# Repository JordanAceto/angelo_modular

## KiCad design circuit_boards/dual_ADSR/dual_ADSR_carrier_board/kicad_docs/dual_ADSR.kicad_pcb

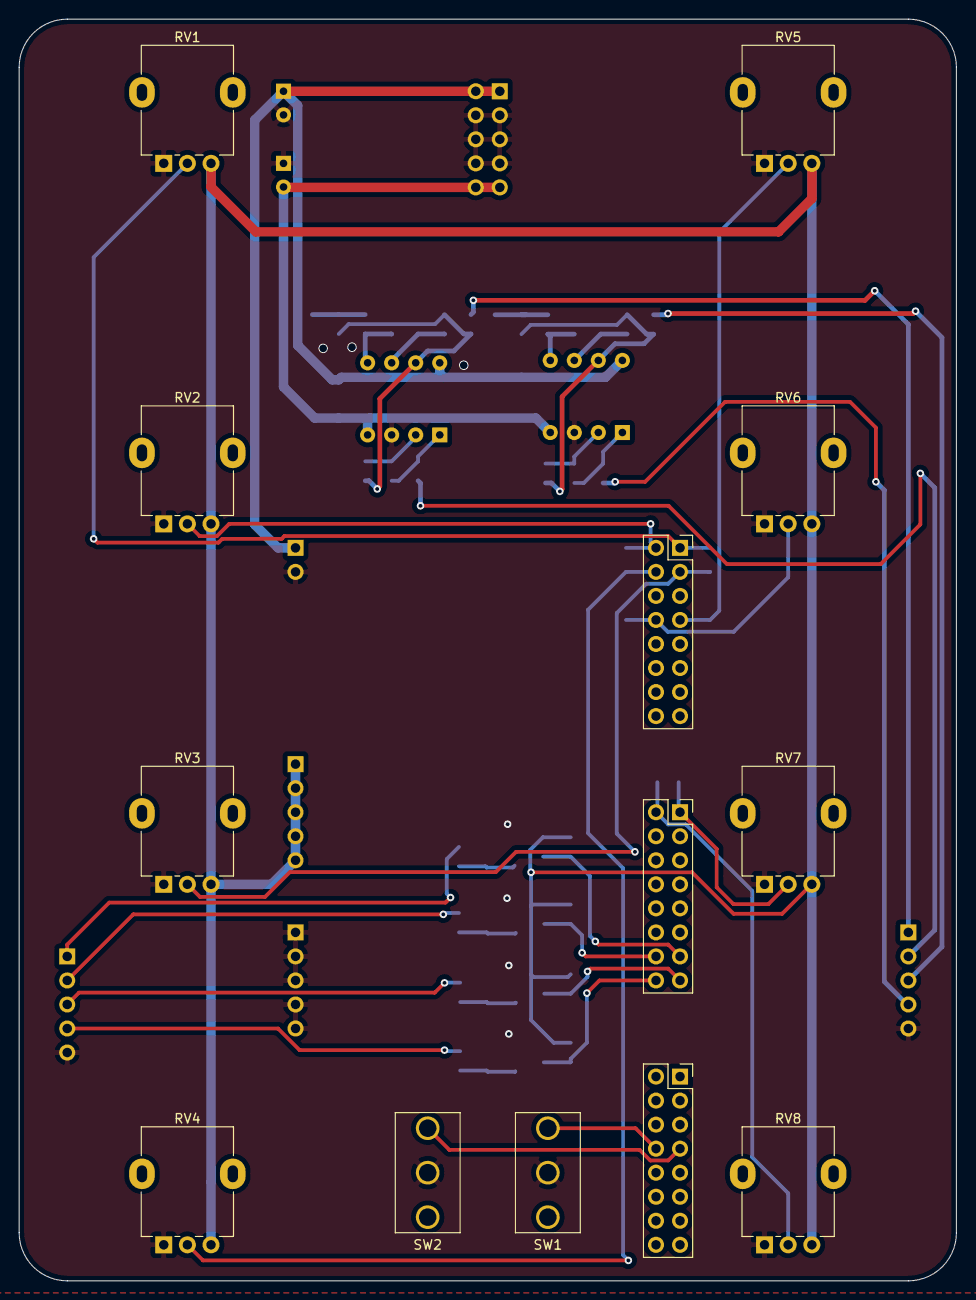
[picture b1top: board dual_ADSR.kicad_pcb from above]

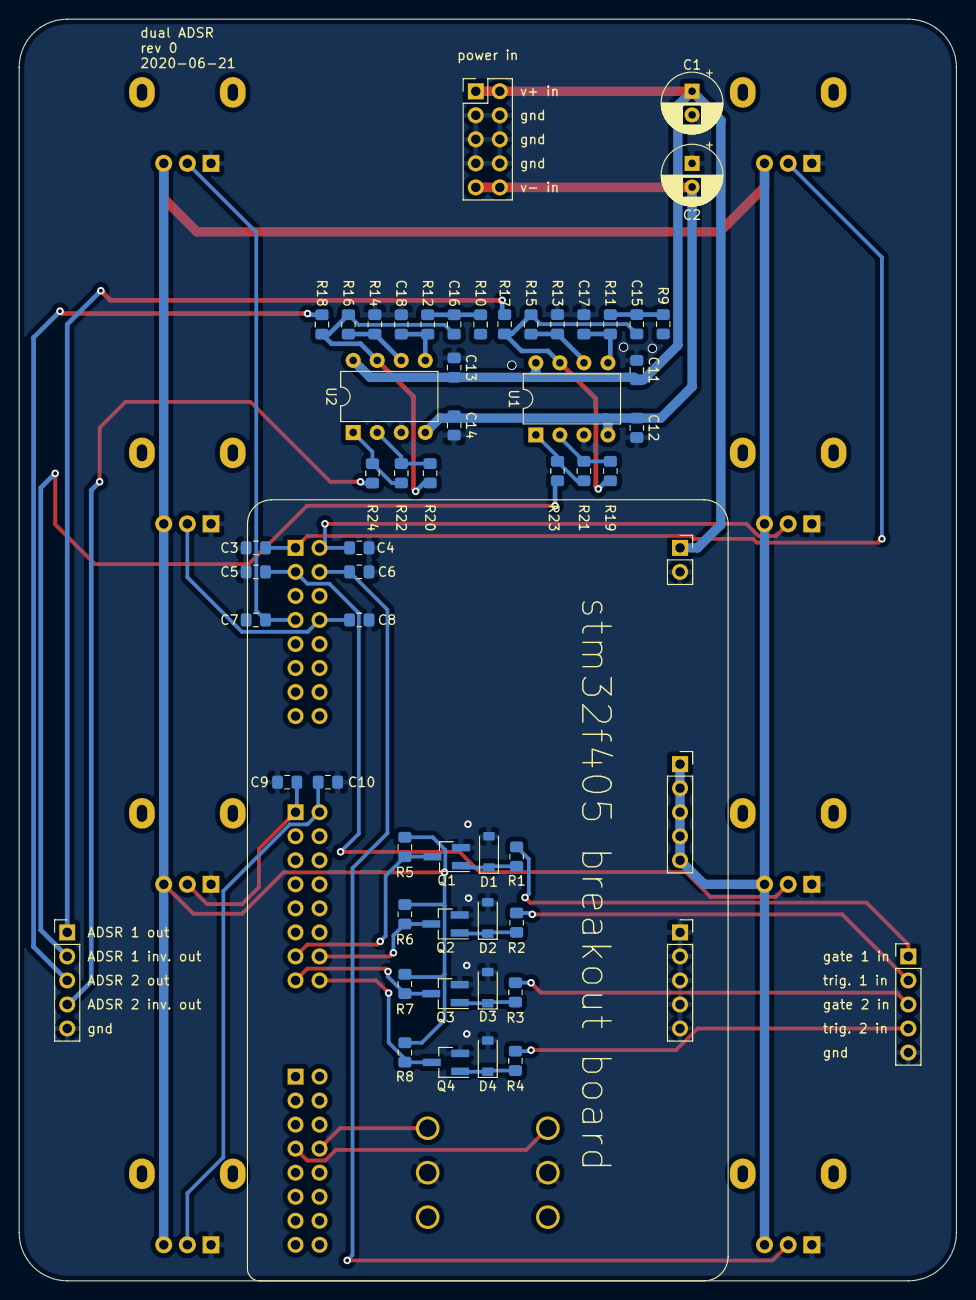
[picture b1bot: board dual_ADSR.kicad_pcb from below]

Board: 2 copper layers, 99.1 x 133.3 mm, 71 parts (58 on the bottom side), 42 nets.

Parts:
C1, C2: 10uF; CP_Radial_D6.3mm_P2.50mm
C3, C4, C5, C6, C7, C8, C9, C10, C11, C12, C13, C14: 100nF; C_0805_2012Metric_Pad1.15x1.40mm_HandSolder
C15, C16, C17, C18: 2n2; C_0805_2012Metric_Pad1.15x1.40mm_HandSolder
D1, D2, D3, D4: 1N4148W; D_SOD-123
J1: inputs; PinHeader_1x05_P2.54mm_Vertical
J2: power_in; PinHeader_2x05_P2.54mm_Vertical
J3: outputs; PinHeader_1x05_P2.54mm_Vertical
J4: stm32_DC_in; PinSocket_1x02_P2.54mm_Vertical
J5: 3.3v; PinSocket_1x05_P2.54mm_Vertical
J6: gnd; PinSocket_1x05_P2.54mm_Vertical
J7: port_A; PinSocket_2x08_P2.54mm_Vertical
J8: port_B; PinSocket_2x08_P2.54mm_Vertical
J9: port_C; PinSocket_2x08_P2.54mm_Vertical
Q1, Q2, Q3, Q4: MMBT3904; SOT-23_Handsoldering
R1, R2, R3, R4, R19, R20, R21, R22: 100k; R_0805_2012Metric_Pad1.15x1.40mm_HandSolder
R5, R6, R7, R8: 10k; R_0805_2012Metric_Pad1.15x1.40mm_HandSolder
R9, R10: 50k; R_0805_2012Metric_Pad1.15x1.40mm_HandSolder
R11, R12: 200k; R_0805_2012Metric_Pad1.15x1.40mm_HandSolder
R13, R14: 33k; R_0805_2012Metric_Pad1.15x1.40mm_HandSolder
R15, R16: 68k; R_0805_2012Metric_Pad1.15x1.40mm_HandSolder
R17, R18, R23, R24: 1k; R_0805_2012Metric_Pad1.15x1.40mm_HandSolder
RV1, RV2, RV3, RV4, RV5, RV6, RV7, RV8: 10k; Potentiometer_Alpha_RD901F-40-00D_Single_Vertical
SW1: range_switch_2; SPDT_on_on
SW2: range_switch_1; SPDT_on_on
U1, U2: TL072; DIP-8_W7.62mm

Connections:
+3V3: J5.1, J5.2, J5.3, J5.4, J5.5, R5.2, R6.2, R7.2, R8.2, RV1.3, RV2.3, RV3.3, RV4.3, RV5.3, RV6.3, RV7.3, RV8.3
+12V: C1.1, C11.1, C13.1, J2.1, J2.2, J4.1, U1.8, U2.8
-12V: C2.2, C12.2, C14.2, J2.9, J2.10, U1.4, U2.4
/gate_and_trigger_inputs/gate_in_1: J1.1, R1.2
/gate_and_trigger_inputs/gate_in_2: J1.3, R3.2
/gate_and_trigger_inputs/inv_trigger_1: J8.14, Q2.3, R6.1
/gate_and_trigger_inputs/inv_trigger_2: J8.16, Q4.3, R8.1
/gate_and_trigger_inputs/trigger_in_1: J1.2, R2.2
/gate_and_trigger_inputs/trigger_in_2: J1.4, R4.2
/opamp_LPFs/ADSR_1_inv_out: J3.2, R23.1
/opamp_LPFs/ADSR_1_out: J3.1, R17.1
/opamp_LPFs/ADSR_2_inv_out: J3.4, R24.1
/opamp_LPFs/ADSR_2_out: J3.3, R18.1
/potentiometers/attack_1: C3.1, J7.1, RV1.2
/potentiometers/attack_2: C7.1, J7.7, RV5.2
/potentiometers/decay_1: C4.1, J7.2, RV2.2
/potentiometers/decay_2: C8.1, J7.8, RV6.2
/potentiometers/release_1: C6.1, J7.4, RV4.2
/potentiometers/release_2: C10.1, J8.2, RV8.2
/potentiometers/sustain_1: C5.1, J7.3, RV3.2
/potentiometers/sustain_2: C9.1, J8.1, RV7.2
/stm32_ports/gate_1: J8.13, Q1.3, R5.1
/stm32_ports/gate_2: J8.15, Q3.3, R7.1
/stm32_ports/range_1: J9.7, SW2.1
/stm32_ports/range_2: J9.8, SW1.1
GND: C1.2, C2.1, C3.2, C4.2, C5.2, C6.2, C7.2, C8.2, C9.2, C10.2, C11.2, C12.1, C13.2, C14.1, C17.2, C18.2, D1.2, D2.2, D3.2, D4.2, J1.5, J2.3, J2.4, J2.5, J2.6, J2.7, J2.8, J3.5, J4.2, J6.1, J6.2, J6.3, J6.4, J6.5, Q1.2, Q2.2, Q3.2, Q4.2, R13.1, R14.1, RV1.1, RV2.1, RV3.1, RV4.1, RV5.1, RV6.1, RV7.1, RV8.1, SW1.2, SW2.2, U1.3, U2.3
unnamed: C15.1, R15.1, R17.2, R19.2, U1.7
unnamed: C15.2, R9.1, R11.2
unnamed: C16.1, R16.1, R18.2, R20.2, U2.7
unnamed: C16.2, R10.1, R12.2
unnamed: C17.1, R11.1, U1.5
unnamed: C18.1, R12.1, U2.5
unnamed: D1.1, Q1.1, R1.1
unnamed: D2.1, Q2.1, R2.1
unnamed: D3.1, Q3.1, R3.1
unnamed: D4.1, Q4.1, R4.1
unnamed: R13.2, R15.2, U1.6
unnamed: R14.2, R16.2, U2.6
unnamed: R19.1, R21.2, U1.2
unnamed: R20.1, R22.2, U2.2
unnamed: R21.1, R23.2, U1.1
unnamed: R22.1, R24.2, U2.1

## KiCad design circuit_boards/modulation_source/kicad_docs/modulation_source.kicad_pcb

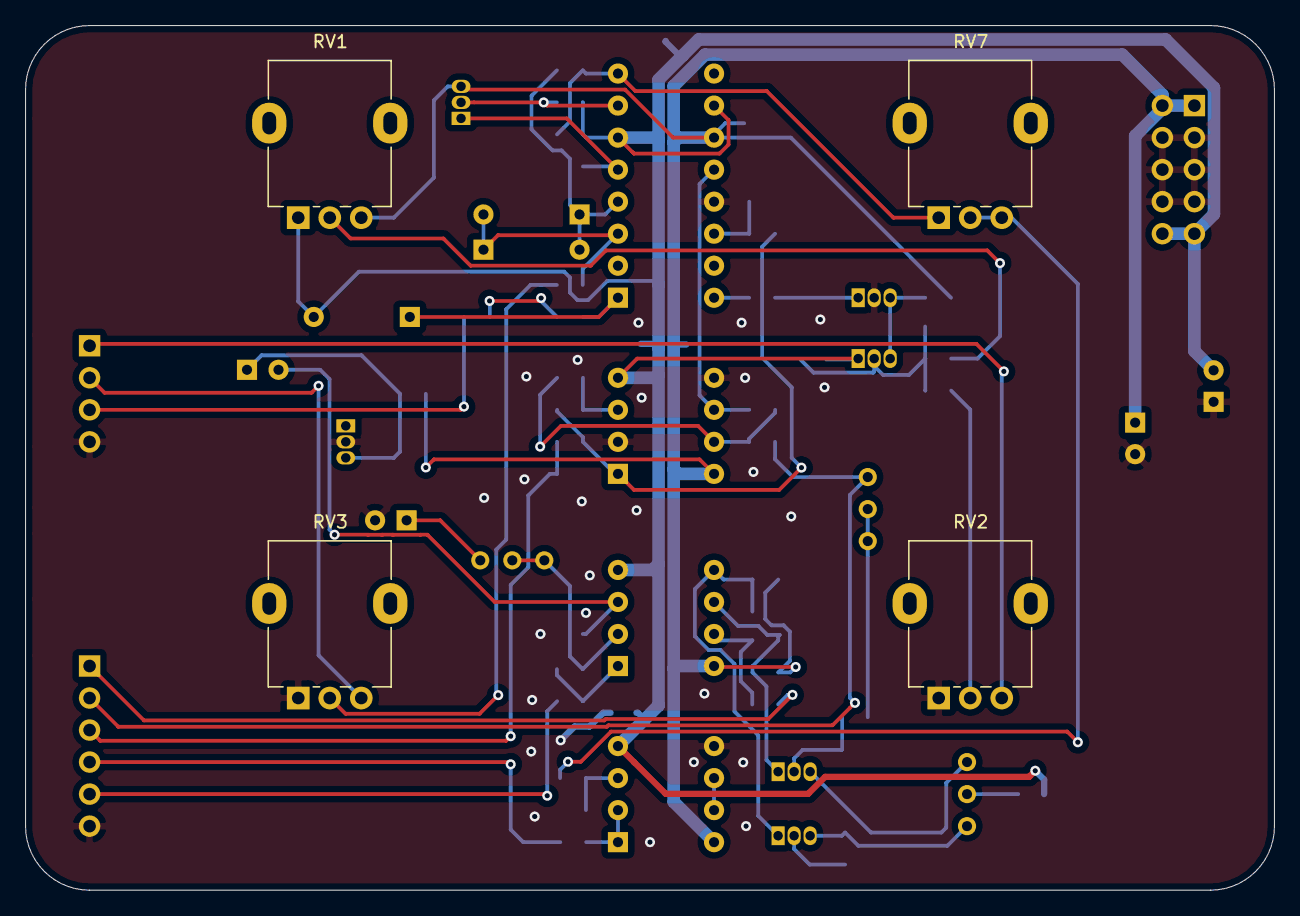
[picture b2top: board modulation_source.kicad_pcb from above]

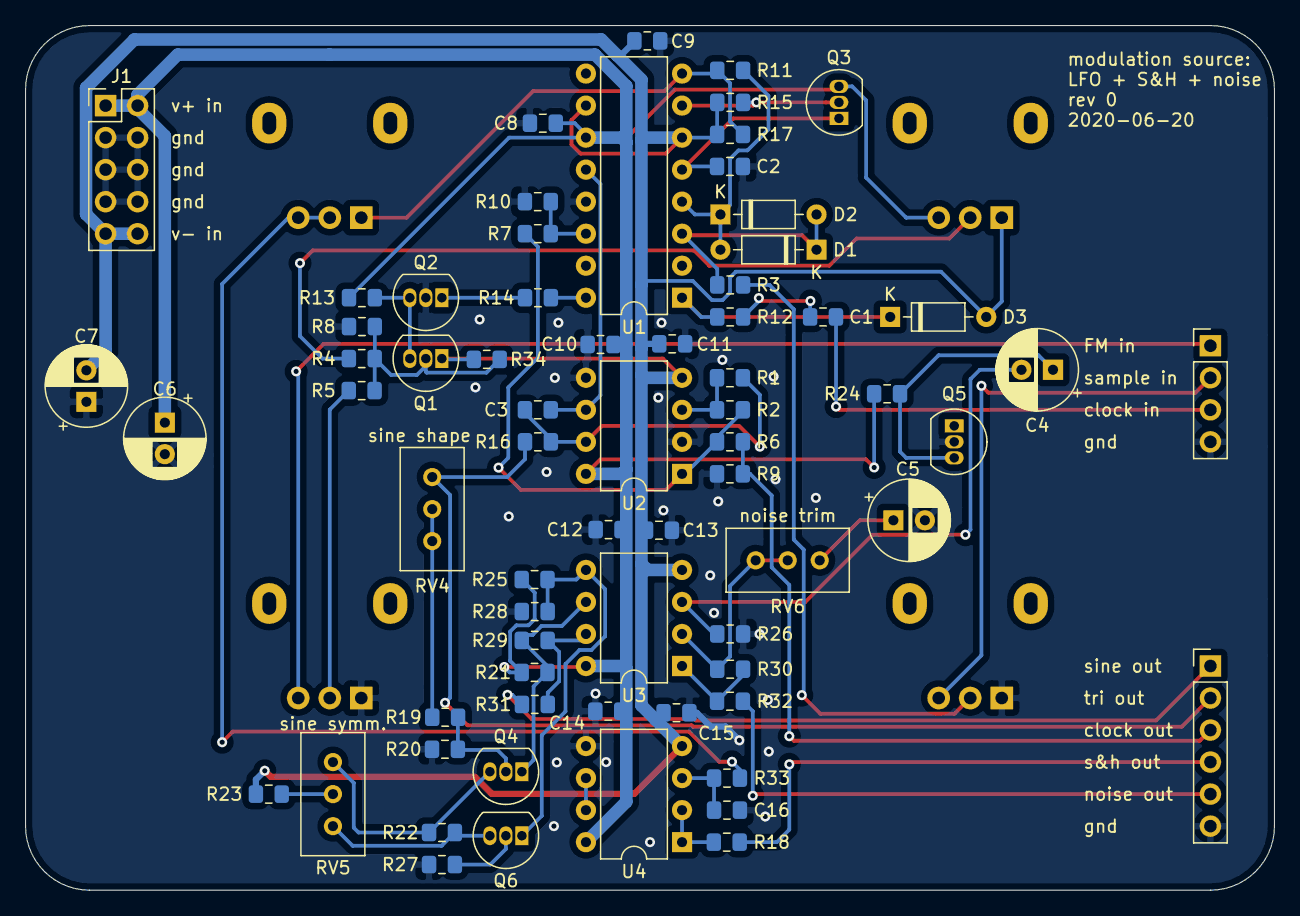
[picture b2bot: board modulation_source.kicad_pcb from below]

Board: 2 copper layers, 99.1 x 68.6 mm, 73 parts (69 on the bottom side), 48 nets.

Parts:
C1, C2: 10nF; C_0805_2012Metric_Pad1.15x1.40mm_HandSolder
C3: 220nF; C_0805_2012Metric_Pad1.15x1.40mm_HandSolder
C4: 47uF; CP_Radial_D6.3mm_P2.50mm
C5: 1uF; CP_Radial_D6.3mm_P2.50mm
C6, C7: 10uF; CP_Radial_D6.3mm_P2.50mm
C8, C9, C10, C11, C12, C13, C14, C15, C16: 100nF; C_0805_2012Metric_Pad1.15x1.40mm_HandSolder
D1, D2, D3: 1N4148; D_DO-35_SOD27_P7.62mm_Horizontal
J1: power_in; PinHeader_2x05_P2.54mm_Vertical
Q1, Q2: BC560; TO-92_Inline
Q3: BF245A; TO-92_Inline
Q4, Q5, Q6: BC550; TO-92_Inline
R1, R5: 100k; R_0805_2012Metric_Pad1.15x1.40mm_HandSolder
R2: 200k; R_0805_2012Metric_Pad1.15x1.40mm_HandSolder
R3, R7, R11, R12: 33k; R_0805_2012Metric_Pad1.15x1.40mm_HandSolder
R4: 270k; R_0805_2012Metric_Pad1.15x1.40mm_HandSolder
R6, R8, R9: 2k; R_0805_2012Metric_Pad1.15x1.40mm_HandSolder
R10, R21, R25: 10k; R_0805_2012Metric_Pad1.15x1.40mm_HandSolder
R13, R14, R17, R28, R29: 15k; R_0805_2012Metric_Pad1.15x1.40mm_HandSolder
R15: 51k; R_0805_2012Metric_Pad1.15x1.40mm_HandSolder
R16, R18, R31, R32, R33: 1k; R_0805_2012Metric_Pad1.15x1.40mm_HandSolder
R19: 27k; R_0805_2012Metric_Pad1.15x1.40mm_HandSolder
R20, R27: 2k2; R_0805_2012Metric_Pad1.15x1.40mm_HandSolder
R22: 390; R_0805_2012Metric_Pad1.15x1.40mm_HandSolder
R23: 18k; R_0805_2012Metric_Pad1.15x1.40mm_HandSolder
R24: 150k; R_0805_2012Metric_Pad1.15x1.40mm_HandSolder
R26: 1M; R_0805_2012Metric_Pad1.15x1.40mm_HandSolder
R30: 10M; R_0805_2012Metric_Pad1.15x1.40mm_HandSolder
R34: 220k; R_0805_2012Metric_Pad1.15x1.40mm_HandSolder
RV1, RV2, RV3: 100k; Potentiometer_Alpha_RD901F-40-00D_Single_Vertical
RV4, RV5: 50k; Potentiometer_Bourns_3296W_Vertical
RV6: 1k; Potentiometer_Bourns_3296W_Vertical
RV7: 1MA; Potentiometer_Alpha_RD901F-40-00D_Single_Vertical
U1: LM13700; DIP-16_W7.62mm
U2, U3, U4: TL072; DIP-8_W7.62mm
inputs1: Conn_01x04; PinHeader_1x04_P2.54mm_Vertical
outputs1: Conn_01x06; PinHeader_1x06_P2.54mm_Vertical

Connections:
+12V: C6.1, C8.1, C10.1, C12.1, C14.1, J1.1, J1.2, Q3.3, R13.1, R21.2, R24.1, R25.2, RV1.3, U1.11, U2.8, U3.8, U4.8
-12V: C7.2, C9.2, C11.2, C13.2, C15.2, D3.2, J1.9, J1.10, Q1.1, R15.1, R17.1, R23.1, R34.2, RV1.1, U1.6, U1.10, U2.4, U3.4, U4.4
FM_in: RV2.3, inputs1.1
GND: C2.1, C5.2, C6.2, C7.1, C8.2, C9.1, C10.2, C11.1, C12.2, C13.1, C14.2, C15.1, C16.2, J1.3, J1.4, J1.5, J1.6, J1.7, J1.8, Q2.2, Q5.2, R8.2, R9.2, R10.2, R20.1, R26.1, R27.1, R28.1, RV2.1, RV3.1, U1.13, U2.2, U2.5, U4.5, inputs1.4, outputs1.6
unnamed: C1.1, R12.2
unnamed: C2.2, Q3.1, U1.5
unnamed: C3.1, R1.1, R16.2, U2.7
unnamed: C3.2, U1.12, U2.6
unnamed: C4.1, Q5.3, R24.2
unnamed: C4.2, R26.2, U3.3
unnamed: C5.1, RV6.3
unnamed: C16.1, R33.1, U4.3
unnamed: D1.1, D2.2, R3.1, U1.3
unnamed: D1.2, D2.1, R11.2, U1.4
unnamed: D3.1, R12.1, U1.1
unnamed: Q1.2, R4.1, R5.1, R8.1, R34.1
unnamed: Q1.3, Q2.3, R13.2
unnamed: Q2.1, R14.1
unnamed: Q3.2, R15.2, U1.7
unnamed: Q4.1, R21.1, R29.2, U3.6
unnamed: Q4.2, R19.2, R20.2
unnamed: Q4.3, R22.1, RV5.3
unnamed: Q6.1, R25.1, R28.2, U3.5
unnamed: Q6.2, R27.2
unnamed: Q6.3, R22.2, RV5.1
unnamed: R1.2, R2.2, U2.3
unnamed: R2.1, R6.2, R7.2, U2.1
unnamed: R3.2, RV3.2
unnamed: R4.2, RV1.2
unnamed: R5.2, RV2.2
unnamed: R7.1, R10.1, U1.14
unnamed: R11.1, R17.2, RV7.1, U1.8
unnamed: R14.2, U1.16
unnamed: R18.2, U4.1, U4.2
unnamed: R19.1, RV4.1, RV4.2
unnamed: R23.2, RV5.2
unnamed: R29.1, R31.2, U3.7
unnamed: R30.1, R32.2, U3.1
unnamed: R30.2, RV6.1, RV6.2, U3.2
unnamed: R33.2, RV7.2, RV7.3
unnamed: U4.6, U4.7
noise_out: R32.1, outputs1.5
s_and_h_out: R18.1, outputs1.4
sample_gate_in: C1.2, inputs1.3
sample_signal_in: RV3.3, inputs1.2
sine_out: R31.1, outputs1.1
square_out: R6.1, R9.1, outputs1.3
tri_out: R16.1, RV4.3, outputs1.2

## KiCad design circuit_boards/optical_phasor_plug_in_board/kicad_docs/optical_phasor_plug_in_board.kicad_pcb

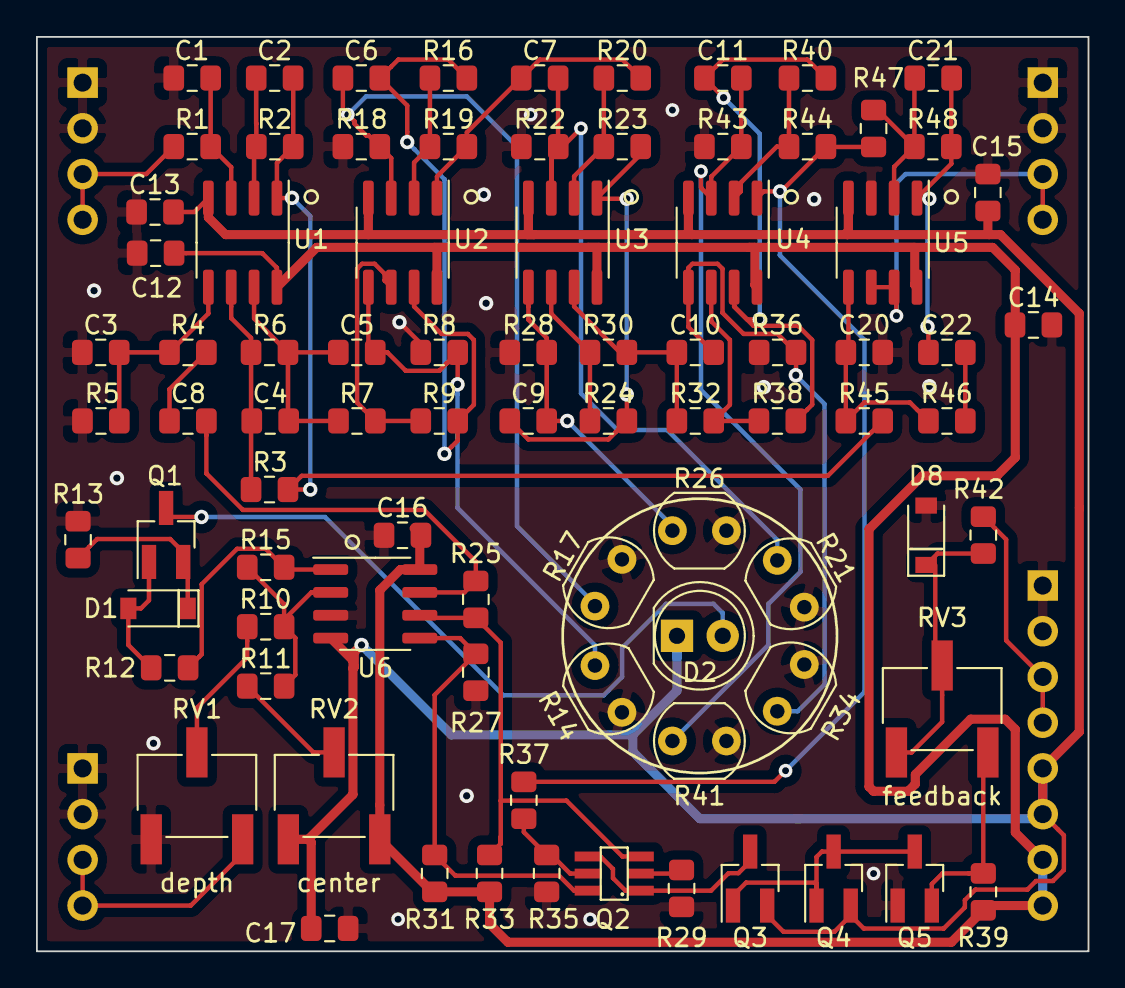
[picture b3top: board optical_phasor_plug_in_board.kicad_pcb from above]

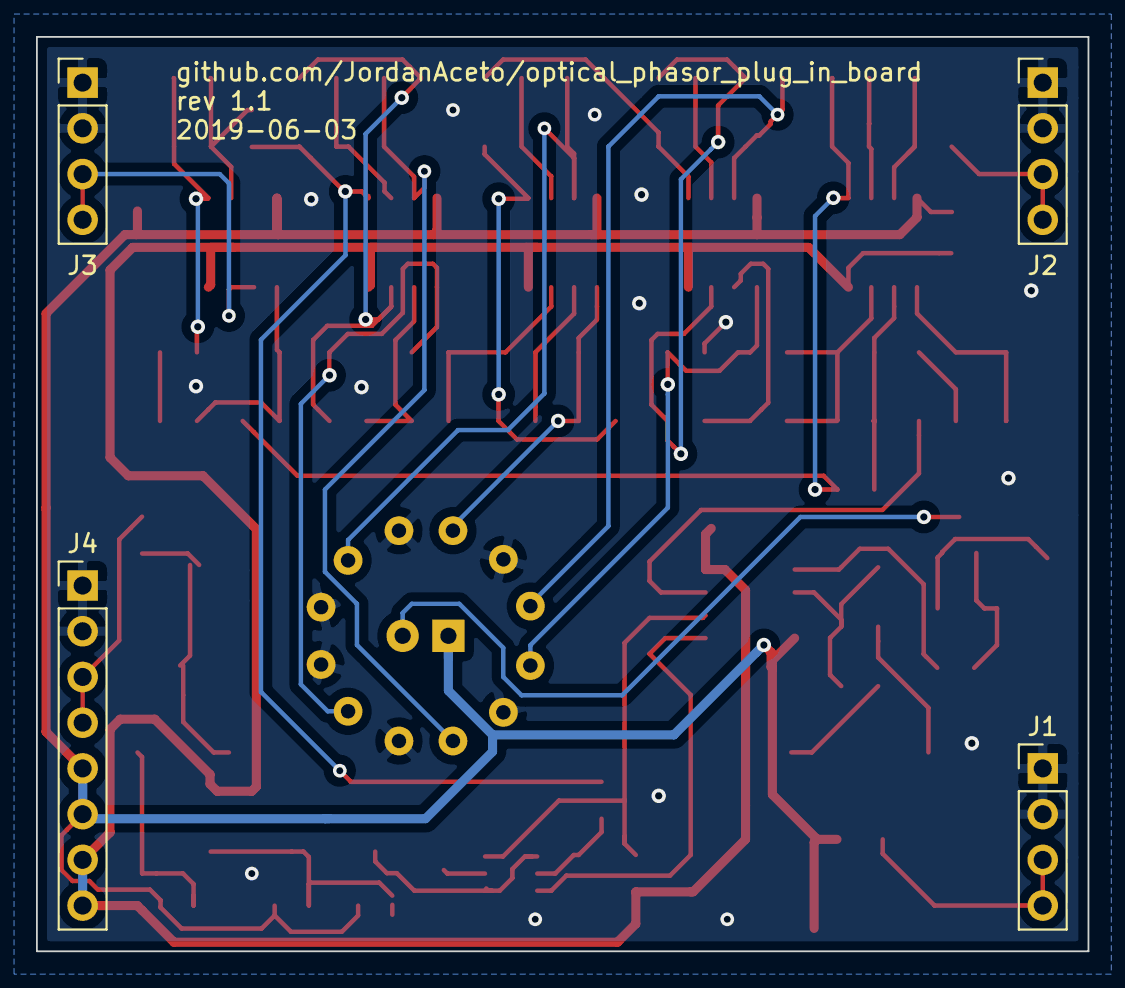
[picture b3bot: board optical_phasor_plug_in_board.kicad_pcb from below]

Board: 2 copper layers, 58.4 x 50.8 mm, 89 parts (4 on the bottom side), 52 nets.

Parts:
C1: 33pF; C_0805_2012Metric_Pad1.15x1.40mm_HandSolder
C2, C12, C13, C14, C15, C16, C17: 100nF; C_0805_2012Metric_Pad1.15x1.40mm_HandSolder
C3: 3n3; C_0805_2012Metric_Pad1.15x1.40mm_HandSolder
C4: 1nF; C_0805_2012Metric_Pad1.15x1.40mm_HandSolder
C5, C6, C7, C9, C10, C11: 6n8; C_0805_2012Metric_Pad1.15x1.40mm_HandSolder
C8: 470nF; C_0805_2012Metric_Pad1.15x1.40mm_HandSolder
C20: 470pF; C_0805_2012Metric_Pad1.15x1.40mm_HandSolder
C21: 1n; C_0805_2012Metric_Pad1.15x1.40mm_HandSolder
C22: 220nF; C_0805_2012Metric_Pad1.15x1.40mm_HandSolder
D1: 1N914; D_SOD-123
D2: green_diffused; LED_D5.0mm
D8: 1N5225B; D_SOD-123
J1, J2, J3: Conn_01x04_Male; PinHeader_1x04_P2.54mm_Vertical
J4: Conn_01x08_Male; PinHeader_1x08_P2.54mm_Vertical
Q1, Q5: MMBT3906; SOT-23_Handsoldering
Q2: BCM847DS135; SOT457
Q3, Q4: MMBT3904; SOT-23_Handsoldering
R1: 3k9; R_0805_2012Metric_Pad1.15x1.40mm_HandSolder
R2: 390k; R_0805_2012Metric_Pad1.15x1.40mm_HandSolder
R3, R6, R7, R9, R16, R19, R20, R23, R24, R30, R32, R38, R40, R44, R46, R47, R48: 4k7; R_0805_2012Metric_Pad1.15x1.40mm_HandSolder
R4: 8k2; R_0805_2012Metric_Pad1.15x1.40mm_HandSolder
R5, R8, R18, R22, R25, R27, R28, R36, R43: 220k; R_0805_2012Metric_Pad1.15x1.40mm_HandSolder
R10, R11, R13, R15: ???; R_0805_2012Metric_Pad1.15x1.40mm_HandSolder
R12: 10k; R_0805_2012Metric_Pad1.15x1.40mm_HandSolder
R14, R17, R21, R26, R34, R41: LDR; R_LDR_5.0x4.1mm_P3mm_Vertical
R29, R35: 220R; R_0805_2012Metric_Pad1.15x1.40mm_HandSolder
R31, R33: 47k; R_0805_2012Metric_Pad1.15x1.40mm_HandSolder
R37: 100k; R_0805_2012Metric_Pad1.15x1.40mm_HandSolder
R39: 680k; R_0805_2012Metric_Pad1.15x1.40mm_HandSolder
R42: 7k5; R_0805_2012Metric_Pad1.15x1.40mm_HandSolder
R45: 12k; R_0805_2012Metric_Pad1.15x1.40mm_HandSolder
RV1: 10k; Potentiometer_Bourns_3269W_Vertical
RV2: 100k; Potentiometer_Bourns_3269W_Vertical
RV3: 50k; Potentiometer_Bourns_3269W_Vertical
U1, U2, U3, U4, U5: RC4558; SOIC-8_3.9x4.9mm_P1.27mm
U6: TL072; SOIC-8_3.9x4.9mm_P1.27mm

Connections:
+12V: C12.1, C14.1, C16.1, J4.7, J4.8, R31.2, R33.2, R39.1, RV2.3, U1.8, U2.8, U3.8, U4.8, U5.8, U6.8
-12V: C13.1, C15.1, C17.1, D2.1, J4.5, J4.6, Q3.2, Q4.2, RV2.1, U1.4, U2.4, U3.4, U4.4, U5.4, U6.4
GND: C1.2, C3.2, C12.2, C13.2, C14.2, C15.2, C16.2, C17.2, C20.1, D8.2, J1.1, J1.2, J2.1, J2.2, J3.1, J3.2, J4.1, J4.2, Q5.1, R5.1, R8.1, R13.2, R14.2, R17.2, R18.1, R21.2, R22.1, R26.2, R27.1, R28.1, R29.1, R34.2, R35.1, R36.1, R41.2, R43.1, RV1.1, U5.3, U6.3
unnamed: C1.1, R1.2, U1.3
unnamed: C2.1, R2.1, R3.2, R45.2, U1.1
unnamed: C2.2, R2.2, U1.2
unnamed: C3.1, R4.2, R5.2, U1.5
unnamed: C4.1, R3.1, R6.2, U1.6
unnamed: C4.2, C5.2, R6.1, R7.2, U1.7
unnamed: C5.1, R8.2, R14.1, U2.5
unnamed: C6.1, R17.1, R18.2, U2.3
unnamed: C6.2, R9.1, R16.2, U2.7
unnamed: C7.1, R21.1, R22.2, U3.3
unnamed: C7.2, R19.1, R20.2, U2.1
unnamed: C8.1, R4.1
unnamed: C8.2, R25.1, U6.7
unnamed: C9.1, R26.1, R28.2, U3.5
unnamed: C9.2, R23.1, R24.2, U3.1
unnamed: C10.1, R34.1, R36.2, U4.5
unnamed: C10.2, R30.1, R32.2, U3.7
unnamed: C11.1, R41.1, R43.2, U4.3
unnamed: C11.2, R38.1, R40.2, U4.7
unnamed: C20.2, R45.1, R46.1, U5.5
unnamed: C21.1, C22.2, R48.1, U5.1
unnamed: C21.2, R47.1, R48.2, U5.2
unnamed: C22.1, R46.2
unnamed: D1.1, Q1.2, R13.1
unnamed: D1.2, Q1.1, R12.1
unnamed: D2.2, Q1.3
unnamed: D8.1, R42.1, RV3.1, RV3.2
unnamed: J1.3, J1.4, RV1.3
unnamed: J2.3, J2.4, R1.1
unnamed: J3.3, J3.4, U5.6, U5.7
unnamed: J4.3, J4.4, R42.2
unnamed: Q2.1, Q2.4, Q3.3
unnamed: Q2.2, R29.2
unnamed: Q2.3, R25.2, R33.1, U6.6
unnamed: Q2.5, R35.2, R37.1
unnamed: Q2.6, R27.2, R31.1, U6.5
unnamed: Q3.1, Q4.1, Q4.3, Q5.3
unnamed: Q5.2, R39.2, RV3.3
unnamed: R7.1, R9.2, U2.6
unnamed: R10.1, R11.1, R15.2, U6.2
unnamed: R10.2, RV1.2
unnamed: R11.2, RV2.2
unnamed: R12.2, R15.1, U6.1
unnamed: R16.1, R19.2, U2.2
unnamed: R20.1, R23.2, U3.2
unnamed: R24.1, R30.2, U3.6
unnamed: R32.1, R38.2, U4.6
unnamed: R37.2, R44.1, R47.2, U4.1
unnamed: R40.1, R44.2, U4.2

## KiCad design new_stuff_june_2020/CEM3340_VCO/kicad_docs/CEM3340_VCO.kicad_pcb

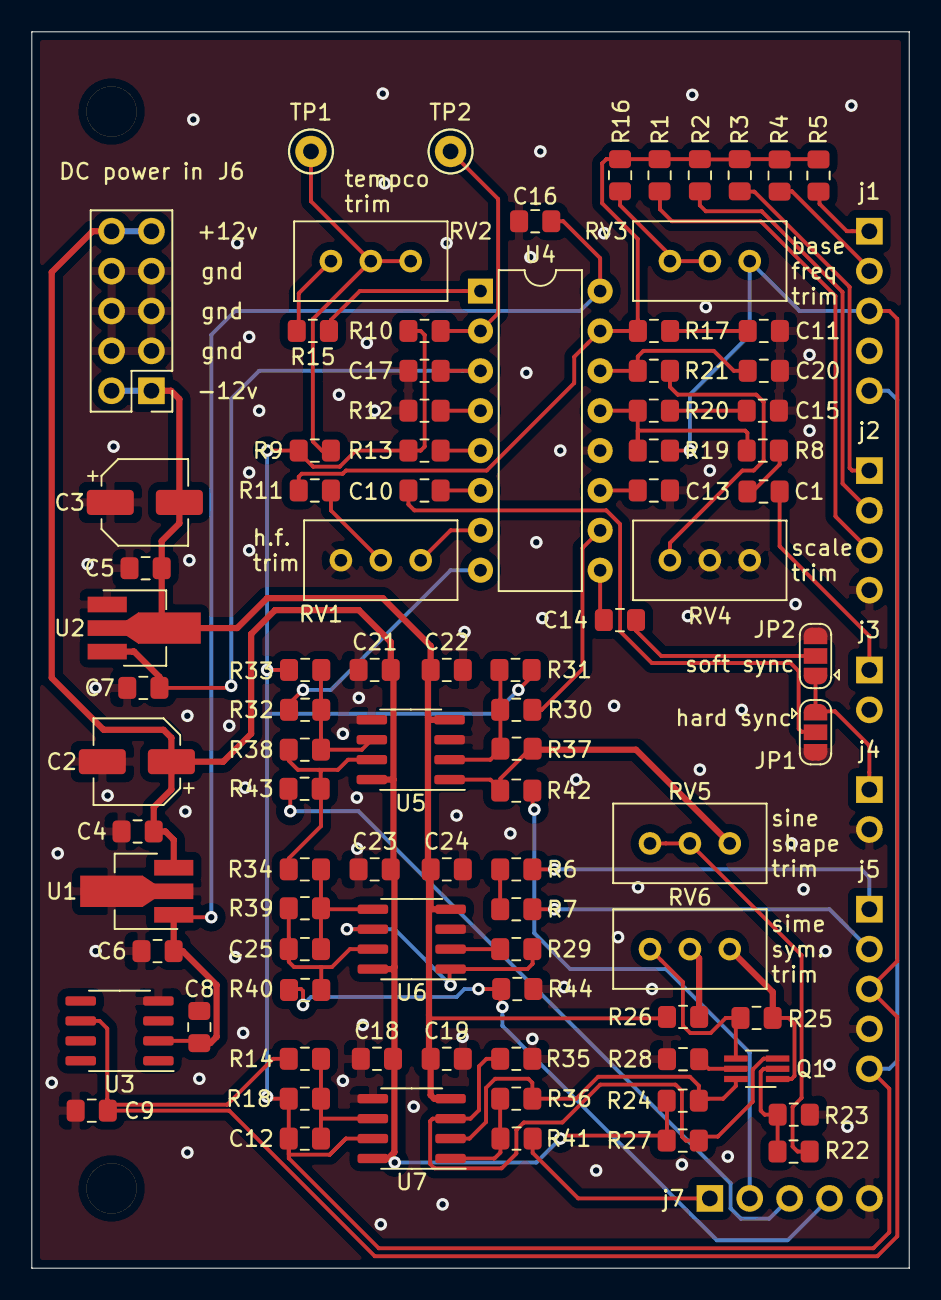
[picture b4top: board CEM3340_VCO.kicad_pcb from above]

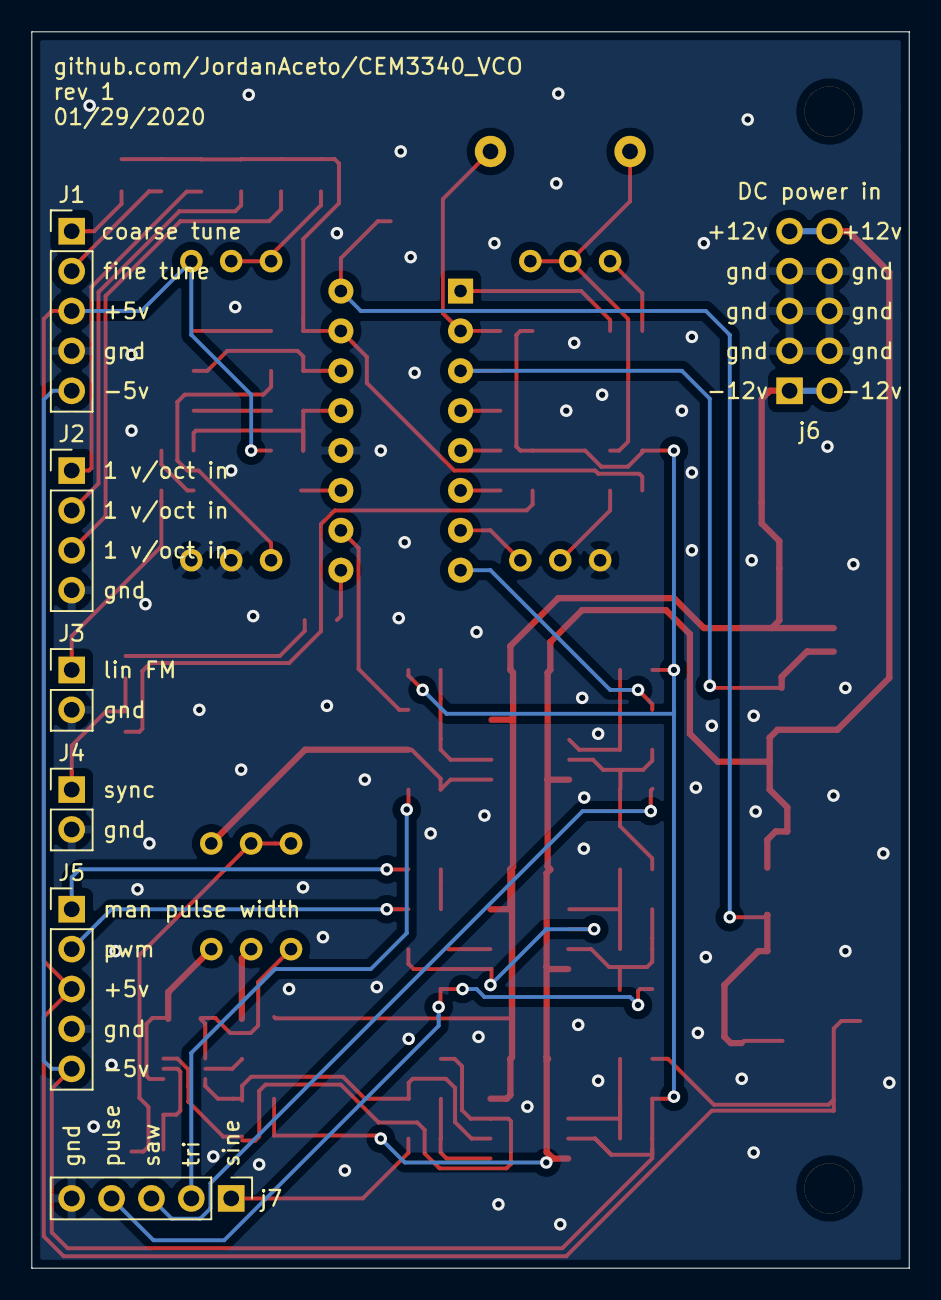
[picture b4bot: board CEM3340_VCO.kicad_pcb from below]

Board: 2 copper layers, 55.9 x 78.7 mm, 96 parts (6 on the bottom side), 62 nets.

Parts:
C1, C4, C5, C6, C7, C8, C9, C16, C17, C18, C19, C21, C22, C23, C24: 100nF; C_0805_2012Metric_Pad1.15x1.40mm_HandSolder
C2, C3: 10uF; CP_Elec_5x5.4
C10, C13, C14: 1nF; C_0805_2012Metric_Pad1.15x1.40mm_HandSolder
C11, C15: 10nF; C_0805_2012Metric_Pad1.15x1.40mm_HandSolder
C12: C; C_0805_2012Metric_Pad1.15x1.40mm_HandSolder
C20: 560pF; C_0805_2012Metric_Pad1.15x1.40mm_HandSolder
C25: 10pF; C_0805_2012Metric_Pad1.15x1.40mm_HandSolder
J1: tuning controls; PinHeader_1x05_P2.54mm_Vertical
J2: 1 v/oct inputs; PinHeader_1x04_P2.54mm_Vertical
J3: linear FM input; PinHeader_1x02_P2.54mm_Vertical
J4: sync input; PinHeader_1x02_P2.54mm_Vertical
J5: PWM inputs; PinHeader_1x05_P2.54mm_Vertical
J6: power input; PinHeader_2x05_P2.54mm_Vertical
JP1: sync sel 1; SolderJumper-3_P1.3mm_Open_RoundedPad1.0x1.5mm
JP2: sync sel 2; SolderJumper-3_P1.3mm_Open_RoundedPad1.0x1.5mm
Q1: MMDT3904; SOT-363_SC-70-6_Handsoldering
R1, R2, R3, R7, R29, R31, R33, R37, R38: 100k; R_0805_2012Metric_Pad1.15x1.40mm_HandSolder
R4, R5, R30, R32: ???; R_0805_2012Metric_Pad1.15x1.40mm_HandSolder
R6: 270k; R_0805_2012Metric_Pad1.15x1.40mm_HandSolder
R8, R11: 1M; R_0805_2012Metric_Pad1.15x1.40mm_HandSolder
R9, R10: 5k6; R_0805_2012Metric_Pad1.15x1.40mm_HandSolder
R12, R13: 51k; R_0805_2012Metric_Pad1.15x1.40mm_HandSolder
R14, R18, R24, R27, R34: 10k; R_0805_2012Metric_Pad1.15x1.40mm_HandSolder
R15, R26: 18k; R_0805_2012Metric_Pad1.15x1.40mm_HandSolder
R16: 82k; R_0805_2012Metric_Pad1.15x1.40mm_HandSolder
R17, R20: 470; R_0805_2012Metric_Pad1.15x1.40mm_HandSolder
R19: 680k; R_0805_2012Metric_Pad1.15x1.40mm_HandSolder
R21: 1k62; R_0805_2012Metric_Pad1.15x1.40mm_HandSolder
R22: 27k; R_0805_2012Metric_Pad1.15x1.40mm_HandSolder
R23, R28: 2k2; R_0805_2012Metric_Pad1.15x1.40mm_HandSolder
R25: 390; R_0805_2012Metric_Pad1.15x1.40mm_HandSolder
R35, R36: 11k; R_0805_2012Metric_Pad1.15x1.40mm_HandSolder
R39: 10M; R_0805_2012Metric_Pad1.15x1.40mm_HandSolder
R40, R44: R; R_0805_2012Metric_Pad1.15x1.40mm_HandSolder
R41, R42, R43: 1k; R_0805_2012Metric_Pad1.15x1.40mm_HandSolder
RV1: 20k; Potentiometer_Bourns_3296W_Vertical
RV2: 5k; Potentiometer_Bourns_3296W_Vertical
RV3, RV5, RV6: 50k; Potentiometer_Bourns_3296W_Vertical
RV4: 500; Potentiometer_Bourns_3296W_Vertical
TP1, TP2: TestPoint; TestPoint_Keystone_5000-5004_Miniature
U1: L78L10_SOT89; SOT-89-3_Handsoldering
U2: MC7905; SOT-89-3_Handsoldering
U3: REF02AU; SOIC-8_3.9x4.9mm_P1.27mm
U4: CEM3340; DIP-16_W7.62mm
U5, U6, U7: TL072; SOIC-8_3.9x4.9mm_P1.27mm
hole 1, hole 2: MountingHole_3.2mm_M3
j7: waveform outputs; PinHeader_1x05_P2.54mm_Vertical

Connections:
+5VA: C9.2, J1.3, J5.3, R14.2, R19.1, RV3.3, U3.6
+10V: C6.2, C8.2, C16.1, U1.1, U3.2, U4.16
+15V: C2.1, C4.1, C18.1, C21.1, C23.1, J6.9, J6.10, R24.1, R27.1, U1.3, U5.8, U6.8, U7.8
-5V: C7.1, C17.2, U2.3, U4.3
-5VA: C12.1, J1.5, J5.5, R9.2, R10.2, R13.2, R18.1, R31.2, R33.2, U7.7
-15V: C3.2, C5.2, C19.2, C22.2, C24.2, J6.1, J6.2, R26.2, U2.2, U5.4, U6.4, U7.4
/Signal_Inputs/expo_cv_i_out: R1.1, R2.1, R3.1, R4.1, R5.1, R11.2, R16.2, R17.2, U4.15
/Signal_Inputs/lin_cv_i_out: R8.1, R19.2, R20.2, U4.13
/Signal_Inputs/pulse_width_i_out: R6.1, R7.1
/VCO_Core/hard_sync_v_in: C10.2, JP1.2
/VCO_Core/soft_sync_v_in: C14.1, JP2.2
/Waveshapers/10vpp_pulse_v_out: R40.1, R44.1, j7.4
/Waveshapers/10vpp_saw_v_out: R43.1, j7.3
/Waveshapers/10vpp_sine_v_out: R41.1, j7.1
/Waveshapers/10vpp_triangle_v_out: R42.1, j7.2
/Waveshapers/raw_saw_v_in: R32.2, U4.8
/Waveshapers/raw_triangle_v_in: R30.2, U4.10
GND: C2.2, C3.1, C4.2, C5.1, C6.1, C7.2, C8.1, C9.1, C11.2, C13.1, C15.2, C16.2, C17.1, C18.2, C19.1, C20.2, C21.2, C22.1, C23.2, C24.1, J1.4, J2.4, J3.2, J4.2, J5.4, J6.3, J6.4, J6.5, J6.6, J6.7, J6.8, JP1.3, JP2.3, R12.2, R23.1, R28.1, R35.1, R44.2, RV1.1, RV4.1, RV4.2, U1.2, U2.1, U3.4, U4.12, U5.3, U5.5, U6.3, U7.5, j7.5
unnamed: C1.1, R8.2
unnamed: C1.2, J3.1
unnamed: C10.1, U4.6
unnamed: C11.1, R17.1
unnamed: C12.2, R14.1, R18.2, U7.6
unnamed: C13.2, U4.11
unnamed: C14.2, U4.9
unnamed: C15.1, R20.1
unnamed: C20.1, R21.1, U4.14
unnamed: C25.1, R39.1, R40.2, U6.7
unnamed: C25.2, R34.1, R39.2, U6.5
unnamed: J1.1, R5.2
unnamed: J1.2, R4.2
unnamed: J2.1, R3.2
unnamed: J2.2, R2.2
unnamed: J2.3, R1.2
unnamed: J4.1, JP1.1, JP2.1
unnamed: J5.1, R6.2
unnamed: J5.2, R7.2
unnamed: Q1.1, R25.1, RV6.3
unnamed: Q1.2, R22.1, R23.2
unnamed: Q1.3, R27.2, R35.2, U7.3
unnamed: Q1.4, R25.2, RV6.1
unnamed: Q1.5, R28.2
unnamed: Q1.6, R24.2, R36.2, U7.2
unnamed: R9.1, RV2.1, RV2.2, TP1.1
unnamed: R10.1, TP2.1, U4.2
unnamed: R11.1, RV1.2
unnamed: R12.1, U4.4
unnamed: R13.1, U4.5
unnamed: R15.1, U4.1
unnamed: R15.2, RV2.3
unnamed: R16.1, RV3.1, RV3.2
unnamed: R21.2, RV4.3
unnamed: R22.2, RV5.1, RV5.2
unnamed: R26.1, RV6.2
unnamed: R29.1, U6.1, U6.6
unnamed: R29.2, U6.2
unnamed: R30.1, R31.1, R37.2, U5.2
unnamed: R32.1, R33.1, R38.2, U5.6
unnamed: R34.2, R38.1, R43.2, U5.7
unnamed: R36.1, R41.2, U7.1
unnamed: R37.1, R42.2, RV5.3, U5.1
unnamed: RV1.3, U4.7

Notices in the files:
circuit_boards/dual_ADSR/dual_ADSR_carrier_board/kicad_docs/dual_ADSR.kicad_pcb:
License: CC by 4.0
circuit_boards/optical_phasor_plug_in_board/kicad_docs/optical_phasor_plug_in_board.kicad_pcb:
Licinse: CC by 4.0
